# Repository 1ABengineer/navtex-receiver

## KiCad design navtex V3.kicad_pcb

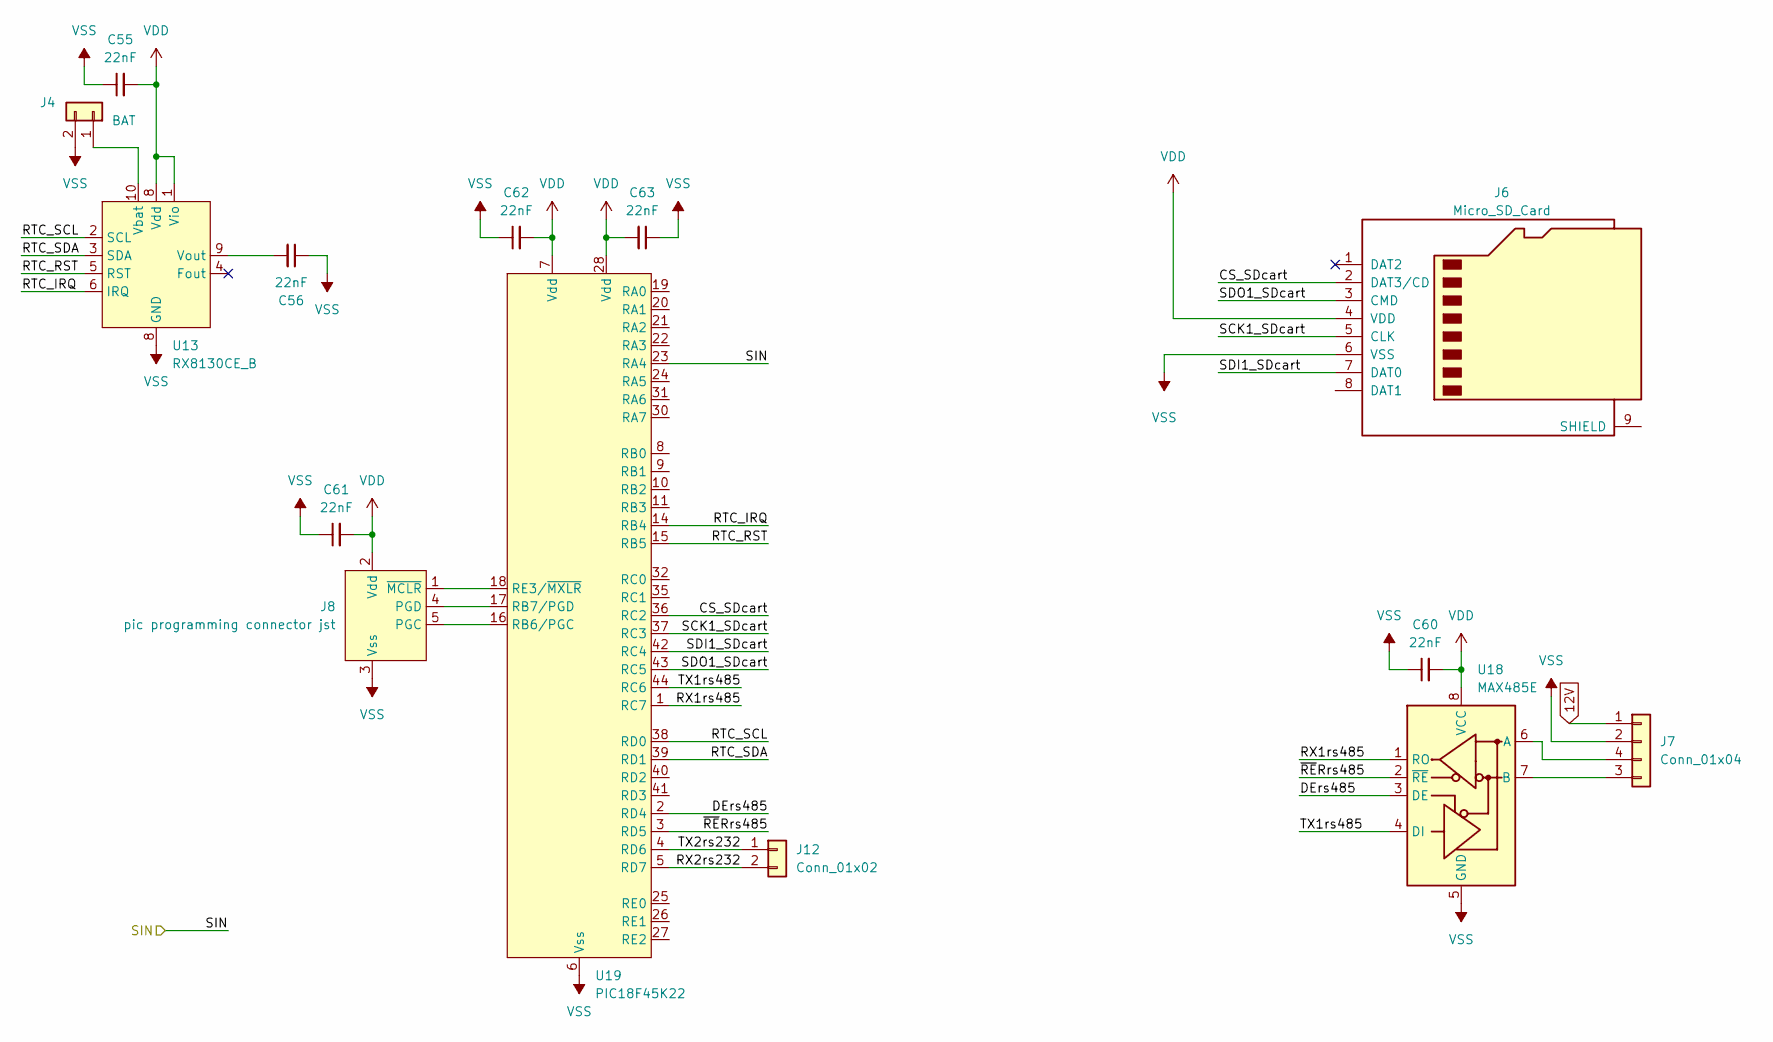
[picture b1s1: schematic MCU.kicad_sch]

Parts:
C55, C56, C60, C61, C62, C63: 22nF; C_0805_2012Metric
J4: BAT; JST_SH_BM02B-SRSS-TB_1x02-1MP_P1.00mm_Vertical
J6: Micro_SD_Card; CONN_47219-2001_MOL
J7: Conn_01x04; AKL 059-04
J8: pic programming connector jst; JST_SH_BM05B-SRSS-TB_1x05-1MP_P1.00mm_Vertical
J12: Conn_01x02; PinHeader_1x02_P2.54mm_Vertical
U13: RX8130CE_B; RX8130CE
U18: MAX485E; SOIC-8_3.9x4.9mm_P1.27mm
U19: PIC18F45K22; TQFP-44_10x10mm_P0.8mm

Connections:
12V: J7.1; also elsewhere on the board
/Untitled Sheet/DECODER/Sin: U19.23 (RA4); also elsewhere on the board
/Untitled Sheet/MCU/CS_SDcart: J6.2 (DAT3/CD), U19.36 (RC2)
/Untitled Sheet/MCU/DErs485: U18.3 (DE), U19.2 (RD4)
/Untitled Sheet/MCU/RTC_IRQ: U13.6 (IRQ), U19.14 (RB4)
/Untitled Sheet/MCU/RTC_RST: U13.5 (RST), U19.15 (RB5)
/Untitled Sheet/MCU/RTC_SCL: U13.2 (SCL), U19.38 (RD0)
/Untitled Sheet/MCU/RTC_SDA: U13.3 (SDA), U19.39 (RD1)
/Untitled Sheet/MCU/RX1rs485: U18.1 (RO), U19.1 (RC7)
/Untitled Sheet/MCU/RX2rs232: J12.2, U19.5 (RD7)
/Untitled Sheet/MCU/SCK1_SDcart: J6.5 (CLK), U19.37 (RC3)
/Untitled Sheet/MCU/SDI1_SDcart: J6.7 (DAT0), U19.42 (RC4)
/Untitled Sheet/MCU/SDO1_SDcart: J6.3 (CMD), U19.43 (RC5)
/Untitled Sheet/MCU/TX1rs485: U18.4 (DI), U19.44 (RC6)
/Untitled Sheet/MCU/TX2rs232: J12.1, U19.4 (RD6)
/Untitled Sheet/MCU/~RERrs485: U18.2 (~RE), U19.3 (RD5)
unnamed: J4.1, U13.10 (Vbat)
unnamed: J7.3, U18.7 (B)
unnamed: J7.4, U18.6 (A)
unnamed: J8.5 (PGC), U19.16 (RB6/PGC)
unnamed: J8.4 (PGD), U19.17 (RB7/PGD)
unnamed: J8.1 (~MCLR), U19.18 (RE3/~MXLR)
unnamed: C56.2, U13.9 (Vout)

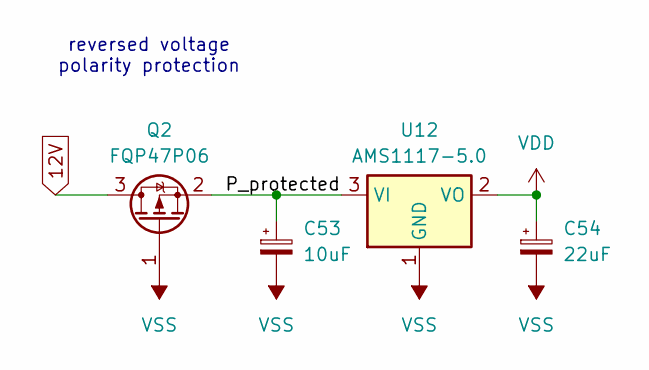
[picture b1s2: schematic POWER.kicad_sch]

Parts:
C53: 10uF; CP_Elec_6.3x5.9
C54: 22uF; CP_Elec_5x5.8
Q2: FQP47P06; TO-220-3_Vertical
U12: AMS1117-5.0; SOT-223-3_TabPin2

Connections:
12V: Q2.3 (s); also elsewhere on the board
/Untitled Sheet/POWER/P_protected: C53.1, Q2.2 (S), U12.3 (VI)

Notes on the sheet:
reversed voltage polarity protection

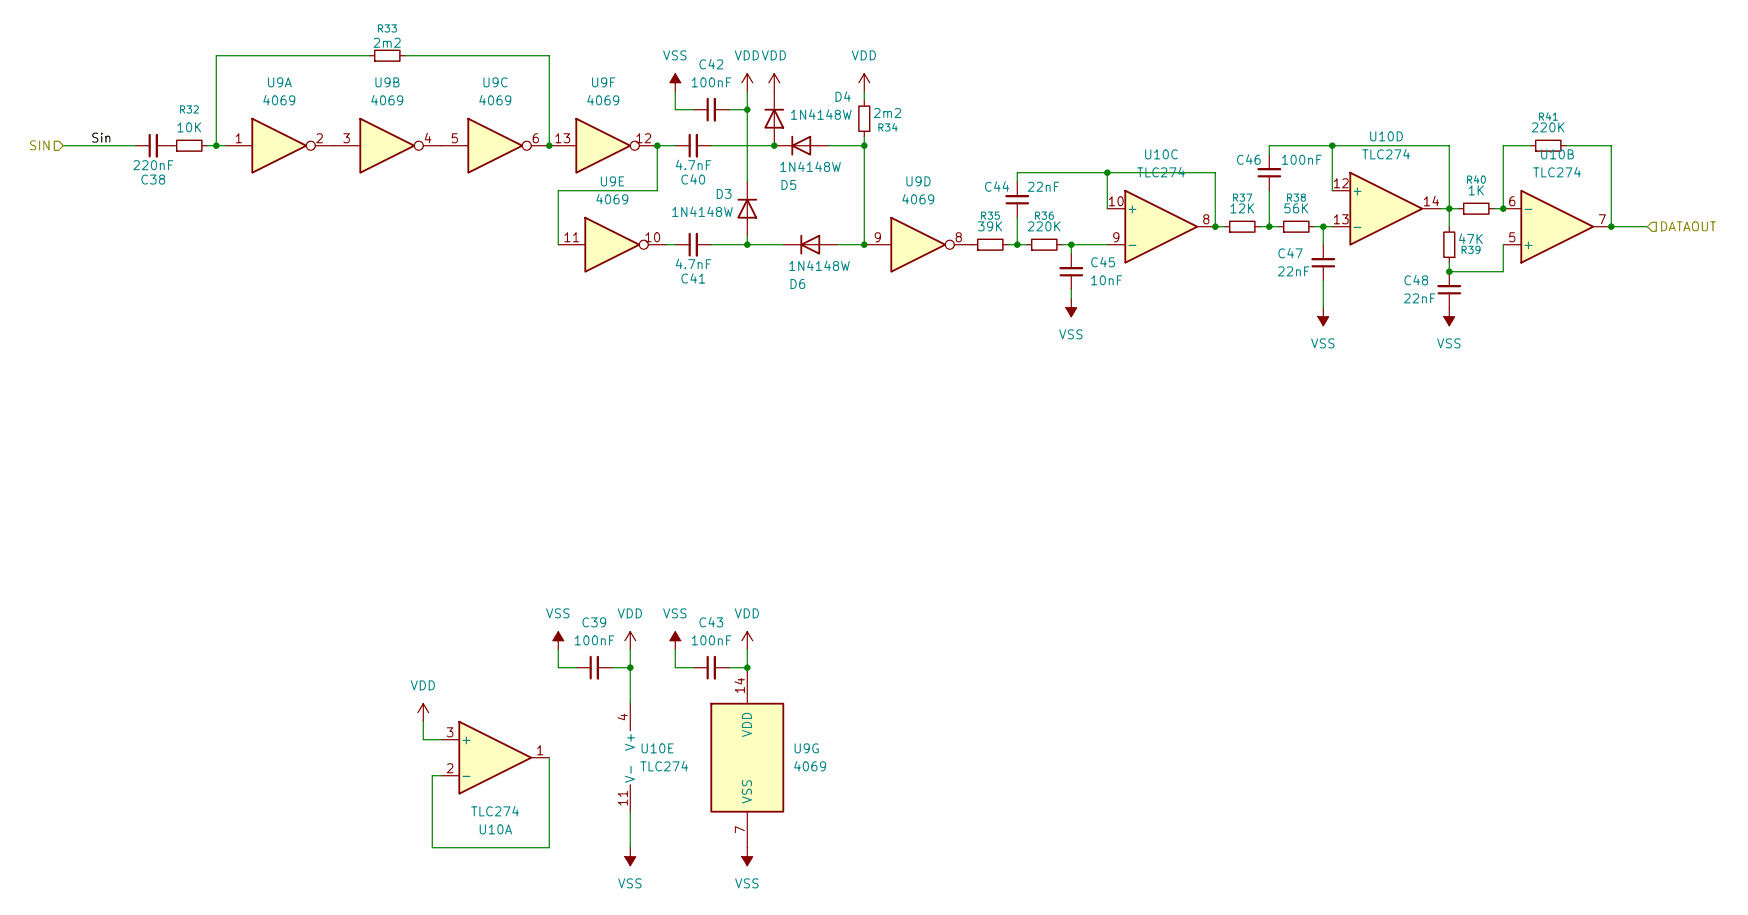
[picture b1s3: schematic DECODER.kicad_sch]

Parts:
C38: 220nF; C_0805_2012Metric
C39, C42, C43, C46: 100nF; C_0805_2012Metric
C40, C41: 4.7nF; C_0805_2012Metric
C44, C47, C48: 22nF; C_0805_2012Metric
C45: 10nF; C_0805_2012Metric
D3, D4, D5, D6: 1N4148W; D_SOD-123
R32: 10K; R_0805_2012Metric
R33, R34: 2m2; R_0805_2012Metric
R35: 39K; R_0805_2012Metric
R36, R41: 220K; R_0805_2012Metric
R37: 12K; R_0805_2012Metric
R38: 56K; R_0805_2012Metric
R39: 47K; R_0805_2012Metric
R40: 1K; R_0805_2012Metric
U9: 4069; CERDIP-14_W7.62mm_SideBrazed_Socket
U10: TLC274; CERDIP-14_W7.62mm_SideBrazed_Socket

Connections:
/Untitled Sheet/DECODER/DATAOUT: R41.2, U10.7
/Untitled Sheet/DECODER/Sin: C38.1; also elsewhere on the board
unnamed: C38.2, R32.1
unnamed: C40.1, U9.11, U9.12
unnamed: C41.1, U9.10
unnamed: C44.1, R35.2, R36.1
unnamed: C46.1, R37.2, R38.1
unnamed: C41.2, D3.2 (A), D6.1 (K)
unnamed: C40.2, D4.2 (A), D5.1 (K)
unnamed: D5.2 (A), D6.2 (A), R34.1, U9.9
unnamed: R32.2, R33.1, U9.1
unnamed: R33.2, U9.6, U9.13
unnamed: R35.1, U9.8
unnamed: U9.2, U9.3
unnamed: U9.4, U9.5
unnamed: U10.1, U10.2 (-)
unnamed: C48.2, R39.1, U10.5 (+)
unnamed: R40.2, R41.1, U10.6 (-)
unnamed: C44.2, R37.1, U10.8, U10.10 (+)
unnamed: C45.2, R36.2, U10.9 (-)
unnamed: C46.2, R39.2, R40.1, U10.12 (+), U10.14
unnamed: C47.2, R38.2, U10.13 (-)

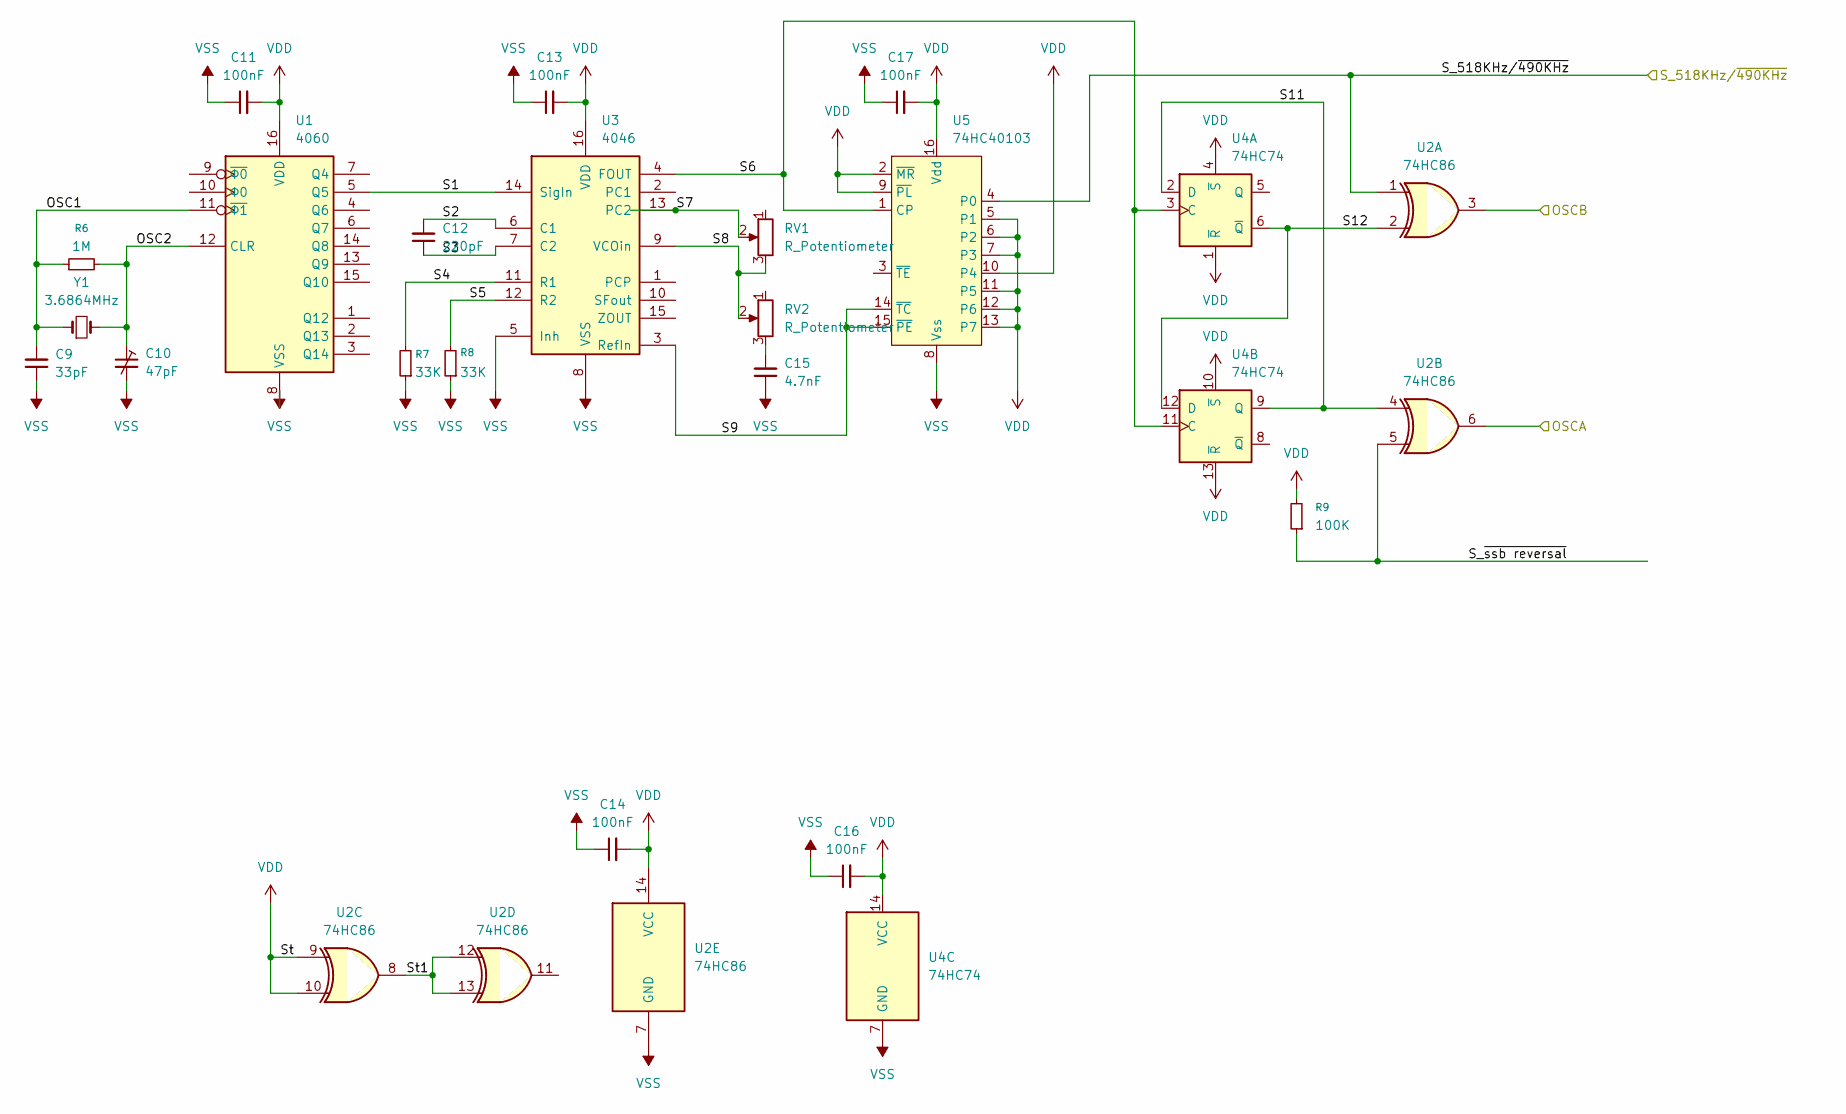
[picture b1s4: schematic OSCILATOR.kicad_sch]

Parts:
C9: 33pF; C_0805_2012Metric
C10: 47pF; C_0805_2012Metric
C11, C13, C14, C16, C17: 100nF; C_0805_2012Metric
C12: 220pF; C_0805_2012Metric
C15: 4.7nF; C_0805_2012Metric
R6: 1M; R_0805_2012Metric
R7, R8: 33K; R_0805_2012Metric
R9: 100K; R_0805_2012Metric
RV1, RV2: R_Potentiometer; model23
U1: 4060; DIP-16_W7.62mm
U2: 74HC86; DIP-14_W7.62mm
U3: 4046; DIP-16_W7.62mm
U4: 74HC74; SO-14_3.9x8.65mm_P1.27mm
U5: 74HC40103; DIP-16_W7.62mm
Y1: 3.6864MHz; cristal p4.88

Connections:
/Untitled Sheet/MIXER/AOSC: U2.6; also elsewhere on the board
/Untitled Sheet/MIXER/BOSC: U2.3; also elsewhere on the board
/Untitled Sheet/OSCILATOR/OSC1: C9.2, R6.1, U1.11 (~Φ1), Y1.1
/Untitled Sheet/OSCILATOR/OSC2: C10.1, R6.2, U1.12 (CLR), Y1.2
/Untitled Sheet/OSCILATOR/S1: U1.5 (Q5), U3.14 (SigIn)
/Untitled Sheet/OSCILATOR/S2: C12.2, U3.6 (C1)
/Untitled Sheet/OSCILATOR/S3: C12.1, U3.7 (C2)
/Untitled Sheet/OSCILATOR/S4: R7.2, U3.11 (R1)
/Untitled Sheet/OSCILATOR/S5: R8.2, U3.12 (R2)
/Untitled Sheet/OSCILATOR/S6: U3.4 (FOUT), U4.3 (C), U4.11 (C), U5.1 (CP)
/Untitled Sheet/OSCILATOR/S7: RV1.2, U3.13 (PC2)
/Untitled Sheet/OSCILATOR/S8: RV1.3, RV2.2, U3.9 (VCOin)
/Untitled Sheet/OSCILATOR/S9: U3.3 (RefIn), U5.14 (~TC), U5.15 (~PE)
/Untitled Sheet/OSCILATOR/S11: U2.4, U4.2 (D), U4.9 (Q)
/Untitled Sheet/OSCILATOR/S12: U2.2, U4.6 (~Q), U4.12 (D)
/Untitled Sheet/OSCILATOR/S_518KHz/~490KHz: U2.1, U5.4 (P0)
/Untitled Sheet/OSCILATOR/S_~ssb reversal: R9.1, U2.5
/Untitled Sheet/OSCILATOR/St1: U2.8, U2.12, U2.13
unnamed: C15.2, RV2.3

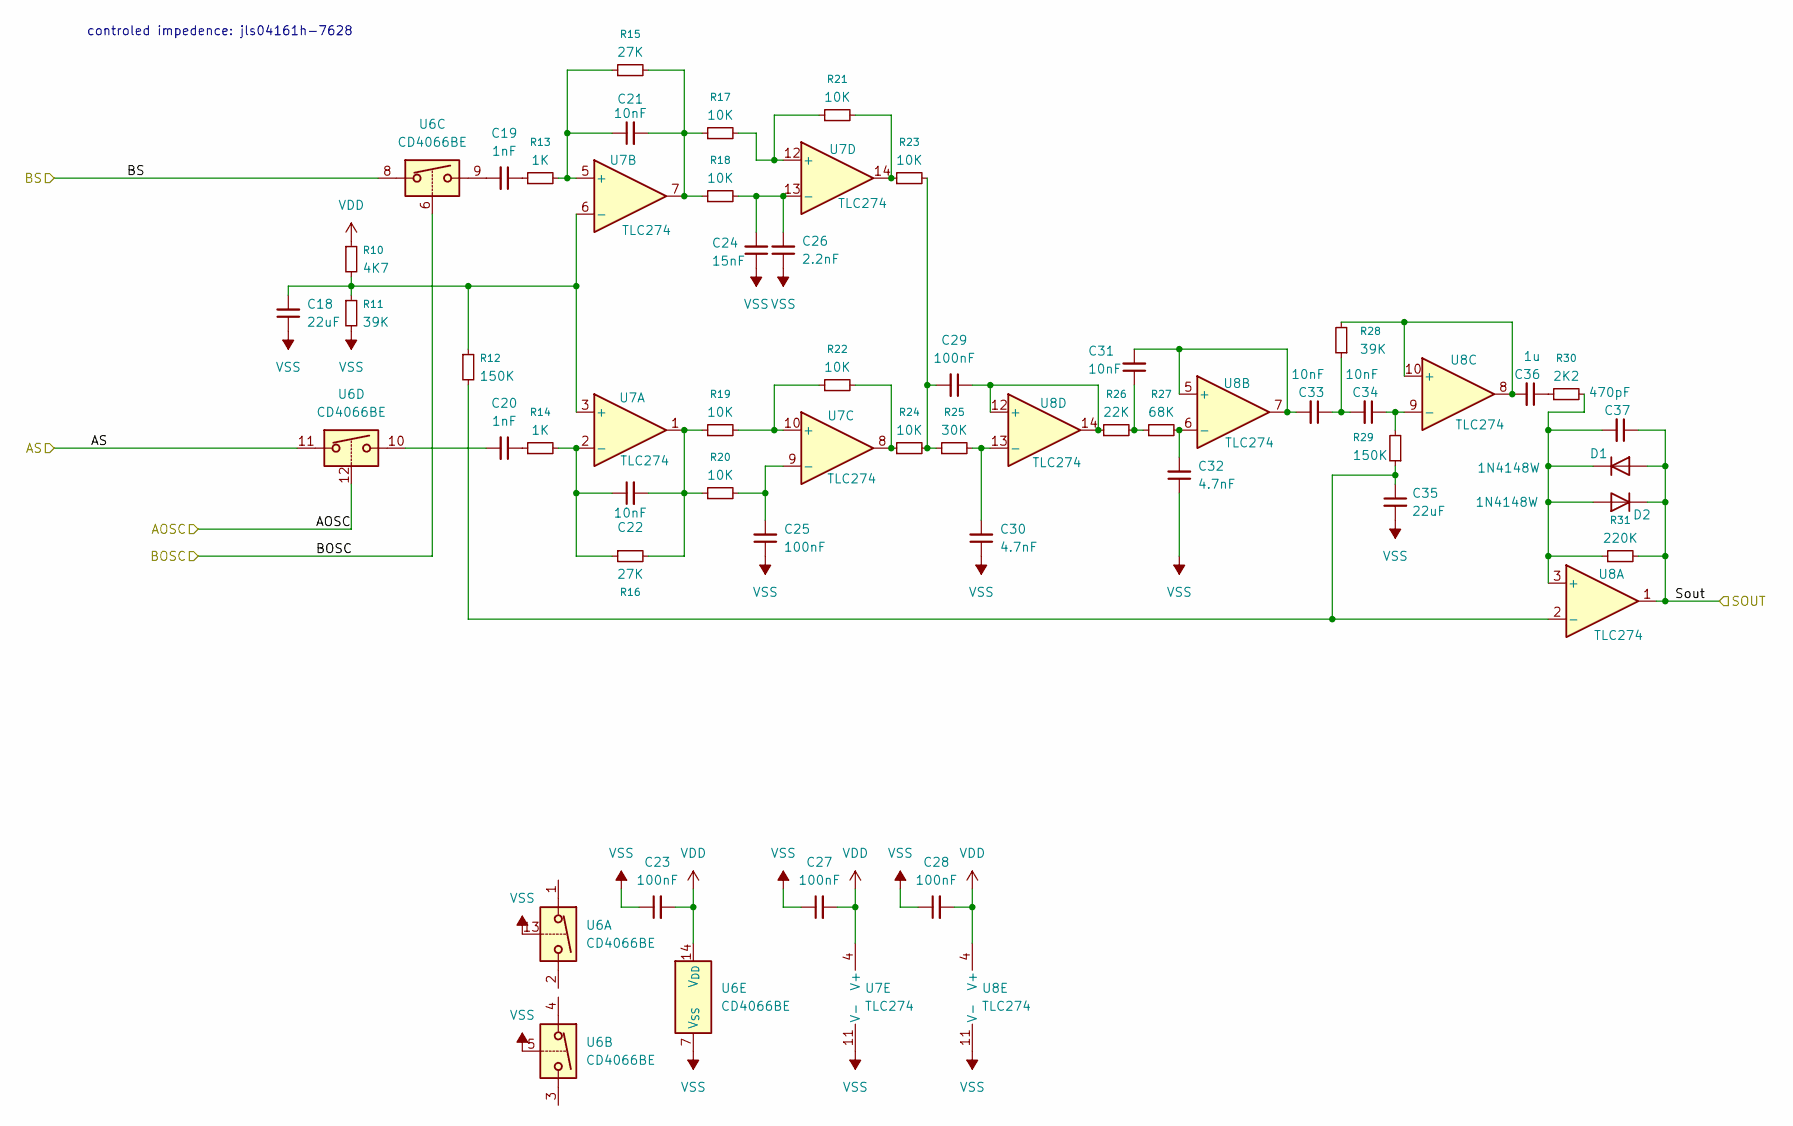
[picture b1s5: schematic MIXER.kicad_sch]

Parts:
C18, C35: 22uF; C_0805_2012Metric
C19, C20: 1nF; C_0805_2012Metric
C21, C22, C31, C33, C34: 10nF; C_0805_2012Metric
C23, C25, C27, C28, C29: 100nF; C_0805_2012Metric
C24: 15nF; C_0805_2012Metric
C26: 2.2nF; C_0805_2012Metric
C30, C32: 4.7nF; C_0805_2012Metric
C36: 1u; C_0805_2012Metric
C37: 470pF; C_0805_2012Metric
D1, D2: 1N4148W; D_SOD-123
R10: 4K7; R_0805_2012Metric
R11, R28: 39K; R_0805_2012Metric
R12, R29: 150K; R_0805_2012Metric
R13, R14: 1K; R_0805_2012Metric
R15, R16: 27K; R_0805_2012Metric
R17, R18, R19, R20, R21, R22, R23, R24: 10K; R_0805_2012Metric
R25: 30K; R_0805_2012Metric
R26: 22K; R_0805_2012Metric
R27: 68K; R_0805_2012Metric
R30: 2K2; R_0805_2012Metric
R31: 220K; R_0805_2012Metric
U6: CD4066BE; DIP-14_W7.62mm
U7, U8: TLC274; DIP-14_W7.62mm

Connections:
/Untitled Sheet/DECODER/Sin: C37.1, D1.2 (A), D2.1 (K), R31.2, U8.1; also elsewhere on the board
/Untitled Sheet/FILTER_PREAMP/A: U6.11; also elsewhere on the board
/Untitled Sheet/FILTER_PREAMP/B: U6.8; also elsewhere on the board
/Untitled Sheet/MIXER/AOSC: U6.12; also elsewhere on the board
/Untitled Sheet/MIXER/BOSC: U6.6; also elsewhere on the board
unnamed: C19.1, R13.1
unnamed: C19.2, U6.9
unnamed: C20.1, R14.1
unnamed: C20.2, U6.10
unnamed: C21.2, R15.2, R17.1, R18.1, U7.7
unnamed: C22.2, R16.2, R19.1, R20.1, U7.1
unnamed: C29.2, R23.2, R24.2, R25.1
unnamed: C31.1, R26.2, R27.1
unnamed: C33.1, C34.2, R28.1
unnamed: C36.1, R30.1
unnamed: C37.2, D1.1 (K), D2.2 (A), R30.2, R31.1, U8.3 (+)
unnamed: R21.2, R23.1, U7.14
unnamed: R22.2, R24.1, U7.8
unnamed: C18.2, R10.2, R11.1, R12.1, U7.3 (+), U7.6 (-)
unnamed: C22.1, R14.2, R16.1, U7.2 (-)
unnamed: C21.1, R13.2, R15.1, U7.5 (+)
unnamed: R19.2, R22.1, U7.10 (+)
unnamed: C25.2, R20.2, U7.9 (-)
unnamed: R17.2, R21.1, U7.12 (+)
unnamed: C24.2, C26.2, R18.2, U7.13 (-)
unnamed: C35.1, R12.2, R29.1, U8.2 (-)
unnamed: C31.2, C33.2, U8.5 (+), U8.7
unnamed: C32.2, R27.2, U8.6 (-)
unnamed: C36.2, R28.2, U8.8, U8.10 (+)
unnamed: C34.1, R29.2, U8.9 (-)
unnamed: C29.1, R26.1, U8.12 (+), U8.14
unnamed: C30.2, R25.2, U8.13 (-)

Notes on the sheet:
controled impedence: jls04161h-7628

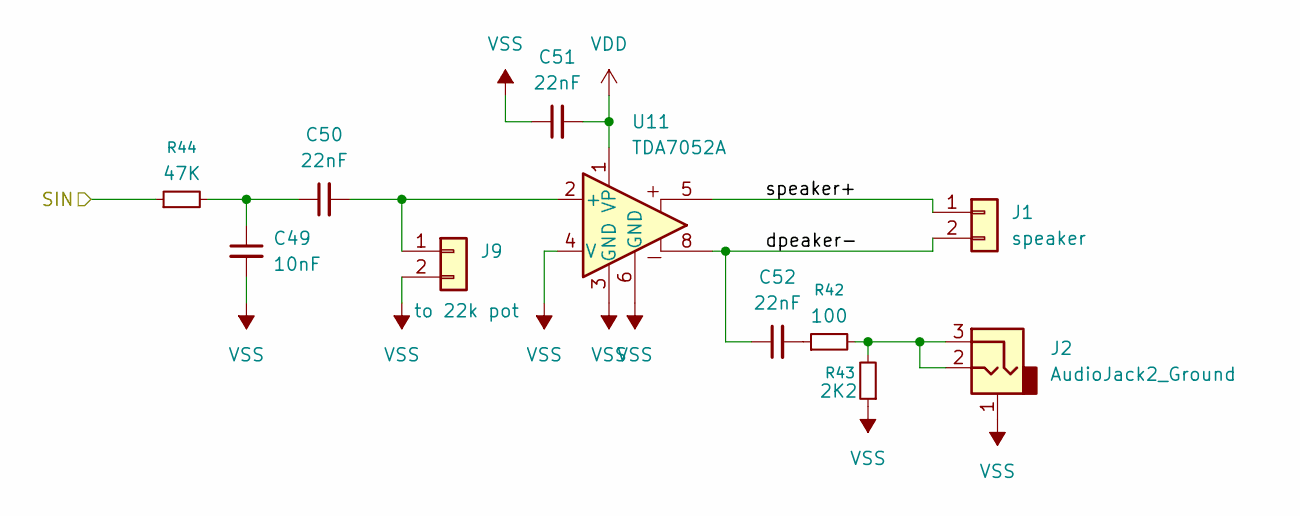
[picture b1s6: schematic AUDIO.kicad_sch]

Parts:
C49: 10nF; C_0805_2012Metric
C50, C51, C52: 22nF; C_0805_2012Metric
J1: speaker; PinHeader_1x02_P2.54mm_Vertical
J2: AudioJack2_Ground; 2.5MM AUDIO JACK
J9: to 22k pot; PinHeader_1x02_P2.54mm_Vertical
R42: 100; R_0805_2012Metric
R43: 2K2; R_0805_2012Metric
R44: 47K; R_0805_2012Metric
U11: TDA7052A; DIP-8_W7.62mm

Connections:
/Untitled Sheet/AUDIO/dpeaker-: C52.1, J1.2, U11.8
/Untitled Sheet/AUDIO/speaker+: J1.1, U11.5
/Untitled Sheet/DECODER/Sin: R44.1; also elsewhere on the board
unnamed: C49.1, C50.1, R44.2
unnamed: C52.2, R42.1
unnamed: J2.2, J2.3, R42.2, R43.2
unnamed: C50.2, J9.1, U11.2 (+)

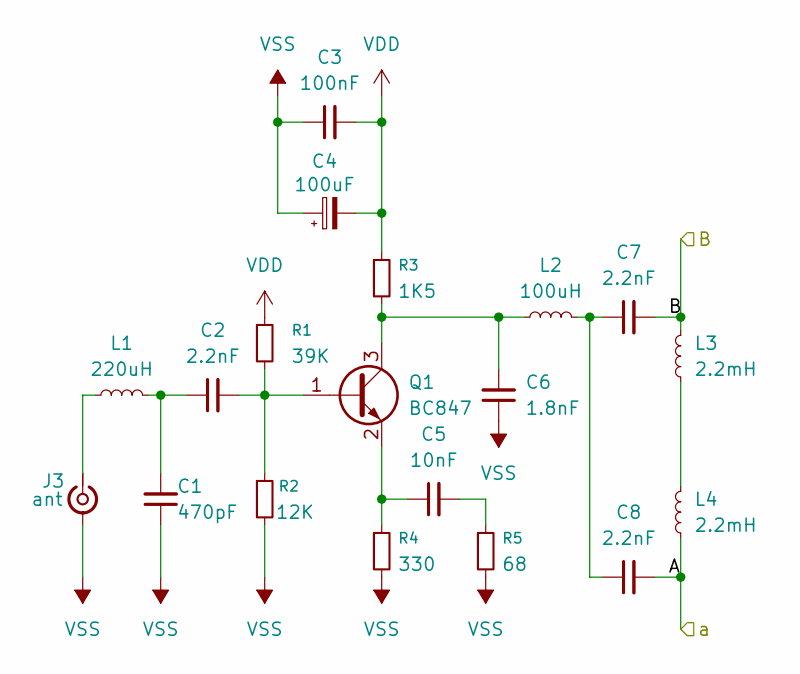
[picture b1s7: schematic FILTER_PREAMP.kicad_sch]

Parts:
C1: 470pF; C_0805_2012Metric
C2, C7, C8: 2.2nF; C_0805_2012Metric
C3: 100nF; C_0805_2012Metric
C4: 100uF; CP_Elec_8x10.5
C5: 10nF; C_0805_2012Metric
C6: 1.8nF; C_0805_2012Metric
J3: ant; SMA_Amphenol_132289_EdgeMount
L1: 220uH; L_Axial_L14.5mm_D5.8mm_P20.32mm_Horizontal_Fastron_HBCC
L2: 100uH; L_Axial_L14.5mm_D5.8mm_P20.32mm_Horizontal_Fastron_HBCC
L3, L4: 2.2mH; L_Axial_L14.5mm_D5.8mm_P20.32mm_Horizontal_Fastron_HBCC
Q1: BC847; SOT-23
R1: 39K; R_0805_2012Metric
R2: 12K; R_0805_2012Metric
R3: 1K5; R_0805_2012Metric
R4: 330; R_0805_2012Metric
R5: 68; R_0805_2012Metric

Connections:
/Untitled Sheet/FILTER_PREAMP/A: C8.2, L4.1; also elsewhere on the board
/Untitled Sheet/FILTER_PREAMP/B: C7.2, L3.2; also elsewhere on the board
unnamed: C1.2, C2.1, L1.2
unnamed: C5.2, R5.1
unnamed: C7.1, C8.1, L2.2
unnamed: J3.1 (In), L1.1
unnamed: L3.1, L4.2
unnamed: C2.2, Q1.1 (B), R1.2, R2.1
unnamed: C6.2, L2.1, Q1.3 (C), R3.2
unnamed: C5.1, Q1.2 (E), R4.1

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
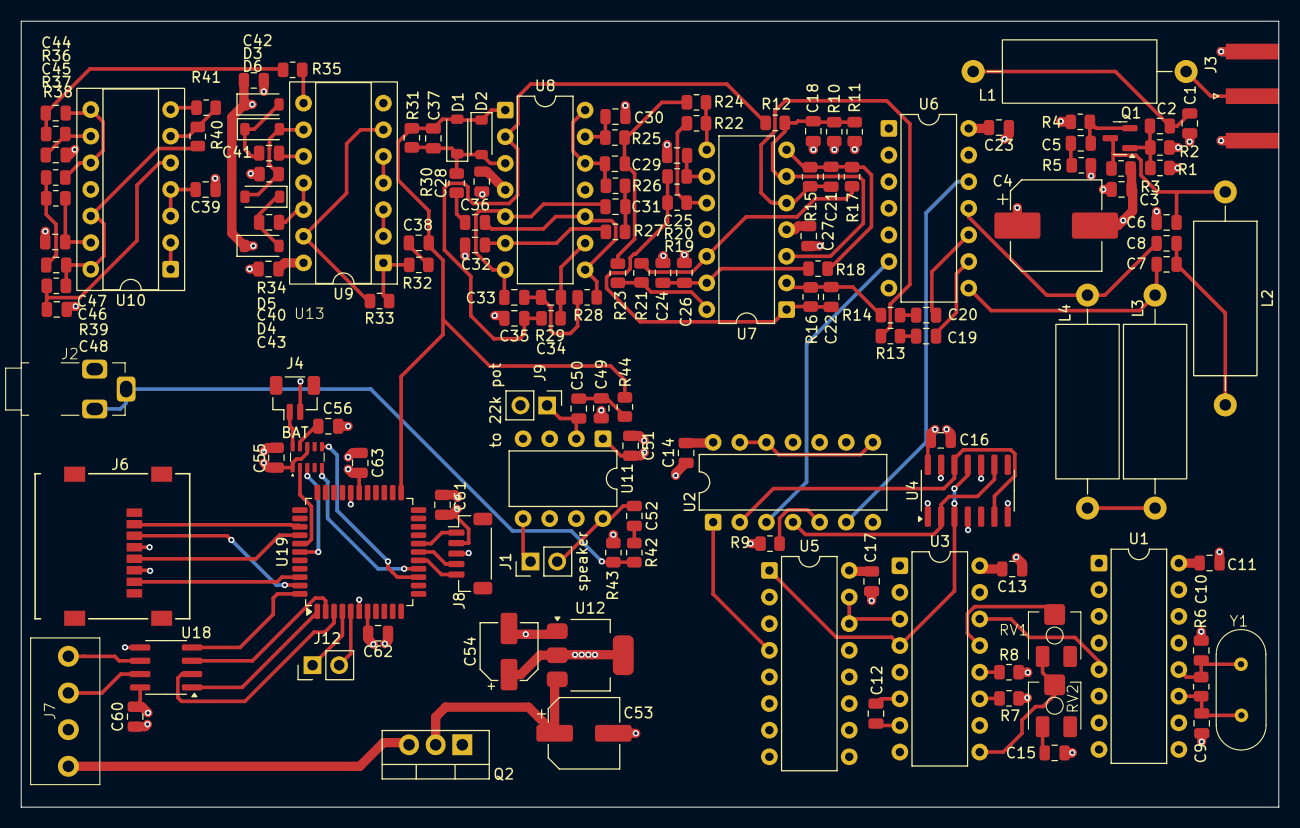
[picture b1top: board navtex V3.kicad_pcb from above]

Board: 4 copper layers, 120.0 x 75.0 mm, 143 parts (0 on the bottom side), 109 nets.

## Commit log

2025-07-19 Updatet md file with imige
